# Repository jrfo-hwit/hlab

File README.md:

# H-Lab

**Laboratório educacional de sistemas embarcados HwIT**

Esta plataforma educacional de sistemas embarcados teve como base de sua placa principal (main_hw) o [BitDogLab](https://github.com/Fruett/BitDogLab) , um projeto totalmente aberto, que permite que os seus usuários copiem, fabriquem, montem e melhorem como bem entenderem.

Este repositório contem todas as informações das evoluções executadas pela HwIT no [BitDogLab](https://github.com/Fruett/BitDogLab) (versões 5.3, 6.0, 6.2, 6.3 - versão do programa [Embarcatech](https://embarcatech.softex.br/) e 6.4 - ultima evolução executada pela HwIT), a próxima versão em desenvolvimento será placa HLab 1.0.

## Placa principal

Além da placa principal [main_hw](./hardware/main_hw/bitdoglab_v6_4_main.pdf), existe a placa do painel frontal de conexão [front_panel_hw](./hardware/front_panel_hw/bitdoglab_v6_4_painel.pdf) compondo a solução [BitDogLab](https://github.com/Fruett/BitDogLab).

## Placas periféricas

Esse repositório apresenta os periféricos desenvolvidos para segunda fase do programa [Embarcatech](https://embarcatech.softex.br/), Os periféricos são compostos pelos seguintes componentes:

* Kit Básico de Periféricos (12 itens)
  * Periferico adaptador de sensores/atuadores
      * [Sensor i2c] Acelerômetro
      * [Sensor i2c] Oxímetro e batimentos cardiácos
      * [Sensor i2c] Medição de distância a Laser
      * [Sensor i2c] Temperatura e pressão
      * [Sensor i2c] Luminosidade
      * [Sensor i2c] Umidade e temperatura
      * [Sensor i2c] Cor RGB
      * [Atuador PWM] Servo Motor
  * Periférico HDMI
  * Periférico de extensão de conexões para sensores (i2c)
  * Periférico teclado matricial (GPIO)
  * Periférico de armazenamento de dados SDCARD (SPI)

* Kit Avançado de Periféricos (19 itens) = Kit Básico (12) + itens abaixo (7)
  * Periférico de extensão de conexões (SPI)
  * Periferico conversor analógico digital ADC / digital analógico DAC / GPIO com oito portas (SPI)
  * Periférico câmera de 2M Pixels (interface paralela)
  * Periférico display LCD 320x240 pixels (SPI)
  * Periférico comunicação radio de longa distância LoRA (SPI)
  * Periférico GPS (UART)
  * Periférico Pi Pico debug probe (SWD)
* Gerenciador de bateria bq25622 (i2c, embarcado na placa principal)

:warning: Acesse esse [link](https://github.com/jrfo-hwit/hlab/tree/main/hardware/peripherals_hw) para obter maiores detalhes sobre cada um dos periféricos

A Placa HLab 1.0 vai integrar a placa principal com o painel frontal, e será evoluida para atender não só as demandas de sistemas embarcados, mas também as demandas de inteligência artifical de borda (EDGE AI) e aprendizado de máquina (Machine Learning), toltamente integradas com os periféricos já desenvolvidos para plataforma atual.

## Micropython

:warning: Esse repositório contém firmwares do interpretador micropython compilado para RP2040 (Pi Pico e Pi Pico W) contida na placa principal, [acesse aqui os últimos releases](https://github.com/jrfo-hwit/hlab/tree/main/firmware/micropython/releases). Esse firmware contém além do micropython todas as bibliotecas necessárias para interagir com a placa principal e seus respectivos periféricos.

**A maneira mais fácil de começar se você é iniciante com a plataforma, é por meio da leitura do nosso [guia do iniciante](./firmware/micropython/README.md).**

## C/C++

Para usuários avançados que desejam utilizar todo o poder do processador RP2040 pode fazer o mesmo por meio da liguagem C++. Se vocês sabe o que está fazendo e gostaria de construir seu próprio projeto de firmware, você deve utilizar o SDK [Pi Pico](https://github.com/raspberrypi/pico-sdk) e pode utilizar nosso [projeto exemplo](https://github.com/jrfo-hwit/hlab/tree/main/firmware/c_cpp/boilerplate), ou se basear em nossos [exemplos de uso da placa principal e/ou periféricos](https://github.com/jrfo-hwit/hlab/tree/main/firmware/c_cpp/examples).

# Licença

Todas as versões BitDogLab estão sob a licença CERN Open Hardware Licence Version 2 - Strongly Reciprocal .
Para mais detalhes veja o arquivo `LICENSE`.

Os demais hardwares periféricos e a futura placa H-Lab estão sob a licença MIT . Para mais detalhes veja o arquivo `LICENSE`.

# Estrutura do Repositório

Segue abaixo a estrutura de arquivos desse repositório. 

O repositório se divide em firmware (código que controla o processador principal da BitDogLab/HLab) contendo tanto código micropython (usuários básicos) quanto c/c++ (usuários avançados), seguido do hardware eletrônico que contém as informações de todas as placas (principal, painel frontal e periféricos), seguido software contendo informações e código para plataforma low code, mecânica contendo peças e partes mecânicas de suporte ao hardware, e fechando com a pasta educacional contendo informações e material para treinamento de professores, instruturoes e alunos.

```bash
├───education "Arquivos e documentação para treinamentos e aprendizado"
│   ├───teacher "Materiais de treinamento para professores"
│   ├───instructor "Materiais de treinamento para instrutores"
│   └───student "Aulas para estudantes"
├───firmware "Nesta pasta ficam os arquivos do firmware, seja micropython ou c/c++"
│   └───micropython "Interpretador (arquivos fonte e uf2 para carregarmos na Pi Pico) e todos exemplos"
│       ├───micropython "Código fonte e compilado do interpretador micropython"
│       ├───pimoroni-pico "Código fonte pimoroni-pico, contendo bilbiotecas e micropython"
│       ├───releases "firmware compilado micropython"
│       └───examples "Arquivos de exemplo de firmware incluindo codigo fonte e documentação"
│   └───c_cpp "Aqui ficam os arquivos do SDK (submodule) e todos os exemplos"
│       ├───pico_sdk "Link simbolico para SDK"
│       └───examples "Arquivos de exemplo de firmware incluindo codigo fonte e documentação"
├───hardware "Aqui ficam todos os arquivos de hardware para placa principal, painel frontal e perifericos"
│   └───main_hw "Esquemático, Layout and Gerber da placa principal, arquivos de projeto"
│       ├───pcb "Arquivos de fabricação do PCB"
│       ├───3D "Arquivos 3D dos componentes da placa"
│       └───electronics "Datasheets e documentação de projeto"
│   ├───front_panel_hw "Esquemático, Layout and Gerber do painel frontal (quando existente), arquivos de projeto"
│       ├───pcb "Arquivos de fabricação do PCB"
│       ├───3D "Arquivos 3D dos componentes da placa"
│       └───electronics "Datasheets e documentação de projeto"
│   └───peripherals_hw "Esquemático, Layout and Gerber dos periféricos, arquivos de projeto"
│       ├───pcb "Arquivos de fabricação do PCB"
│       ├───3D "Arquivos 3D dos componentes da placa"
│       └───electronics "Datasheets e documentação de projeto"
├───mechanics "Modelos mecânicos para uso com placas da plataforma"
│   ├───main_mech "Partes mecanicas para uso com a placa principal"
│   └───peripherals_mech "Partes mecanicas para uso com os periféricos"
└───software "Softwares de auxilio ao uso da plataforma"
│   └───low_code "Ferramenta de programação em blocos (low code), codigo fonte, biblioteca e documentos"
```

# [Hardware Innovation Technologies](http://www.hwit.com.br/)

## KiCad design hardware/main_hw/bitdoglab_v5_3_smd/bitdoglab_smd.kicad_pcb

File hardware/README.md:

# HLab Hardware

Essa pasta apresenta detalhes sobre todos os relativos a plataforma HLAB e trabalhos anteriores no suporte da bitdoglab.

Basicamente com relação ao bitdoglab, suportamos a evolução da placa a partir da versão 5.3 até a versão 6.3 (embarcatech) e 6.4. Os arquivos esquemáticos da placa principal se encontram na pasta main_hw, nos seguintes links:

* bitdoglab 5.3 [esquemático](./main_hw/bitdoglab_v5_3_smd.pdf) e [código fonte (Kicad)](./main_hw/bitdoglab_v5_3_smd/)
* bitdoglab 6.0 [esquemático](./main_hw/bitdoglab_v6_0_smd.pdf)
* bitdoglab 6.2 [esquemático](./main_hw/bitdoglab_v6_2_smd.pdf)
* bitdoglab 6.3 - versão embarcatech [esquemático](./main_hw/bitdoglab_v6_3_smd-embarcatech.pdf)
* bitdoglab 6.4 [esquemático](./main_hw/bitdoglab_v6_4_main.pdf)

Os arquivos esquemáticos da placa do painel frontal se encontra na pasta front_panel_hw e no seguinte [link](./front_panel_hw/bitdoglab_v6_4_painel.pdf).

Os periféricos são compostos pelos seguintes componentes e seus respectivos links para os esquemáticos:

* Kit Básico de Periféricos (12 itens)
  * [Esquemático](./peripherals_hw/Adaptadora_R1.1.pdf) Periferico adaptador de sensores/atuadores
      * [Sensor i2c] Acelerômetro
      * [Sensor i2c] Oxímetro e batimentos cardiácos
      * [Sensor i2c] Medição de distância a Laser
      * [Sensor i2c] Temperatura e pressão
      * [Sensor i2c] Luminosidade
      * [Sensor i2c] Umidade e temperatura
      * [Sensor i2c] Cor RGB
      * [Atuador PWM] Servo Motor
  * [Esquemático](./peripherals_hw/bitdoglab-dvi-hdmi_v1r1.pdf) Periférico HDMI-DVI
  * [Esquemático](./peripherals_hw/I2C_Extender_R1.1.pdf) Periférico de extensão de conexões para sensores (i2c)
  * [Esquemático](./peripherals_hw/PRJ_Teclado.pdf) Periférico teclado matricial (GPIO)
  * [Esquemático](./peripherals_hw/LS_R1.1.pdf) Periférico de armazenamento de dados SDCARD (SPI)
* Kit Avançado de Periféricos (19 itens) = Kit Básico (12) + itens abaixo (7)
  * [Esquemático](./peripherals_hw/ADC_DAC_R1.1.pdf) Periferico conversor analógico digital ADC / digital analógico DAC / GPIO com oito portas (SPI)
  * [Esquemático](./peripherals_hw/CAMERA.pdf) Periférico câmera de 2M Pixels (interface paralela)
  * [Esquemático](./peripherals_hw/LCD_Rev1.2.pdf) Periférico display LCD 320x240 pixels (SPI)
  * [Esquemático](./peripherals_hw/LS_R1.1.pdf) Periférico comunicação radio de longa distância LoRA (SPI)
  * [Esquemático](./peripherals_hw/Adaptadora_R1.1.pdf) Periférico GPS (UART)
  * [Esquemático](./peripherals_hw/DEBUGGER_R1.1.pdf) Periférico Pi Pico debug probe (SWD)
  * [Esquemático](./peripherals_hw/IDC_Extender_R1.1.pdf) Periférico de extensão de conexões (SPI)
* Gerenciador de bateria bq25622 (i2c, embarcado na placa principal)

# [Hardware Innovation Technologies](http://www.hwit.com.br/)

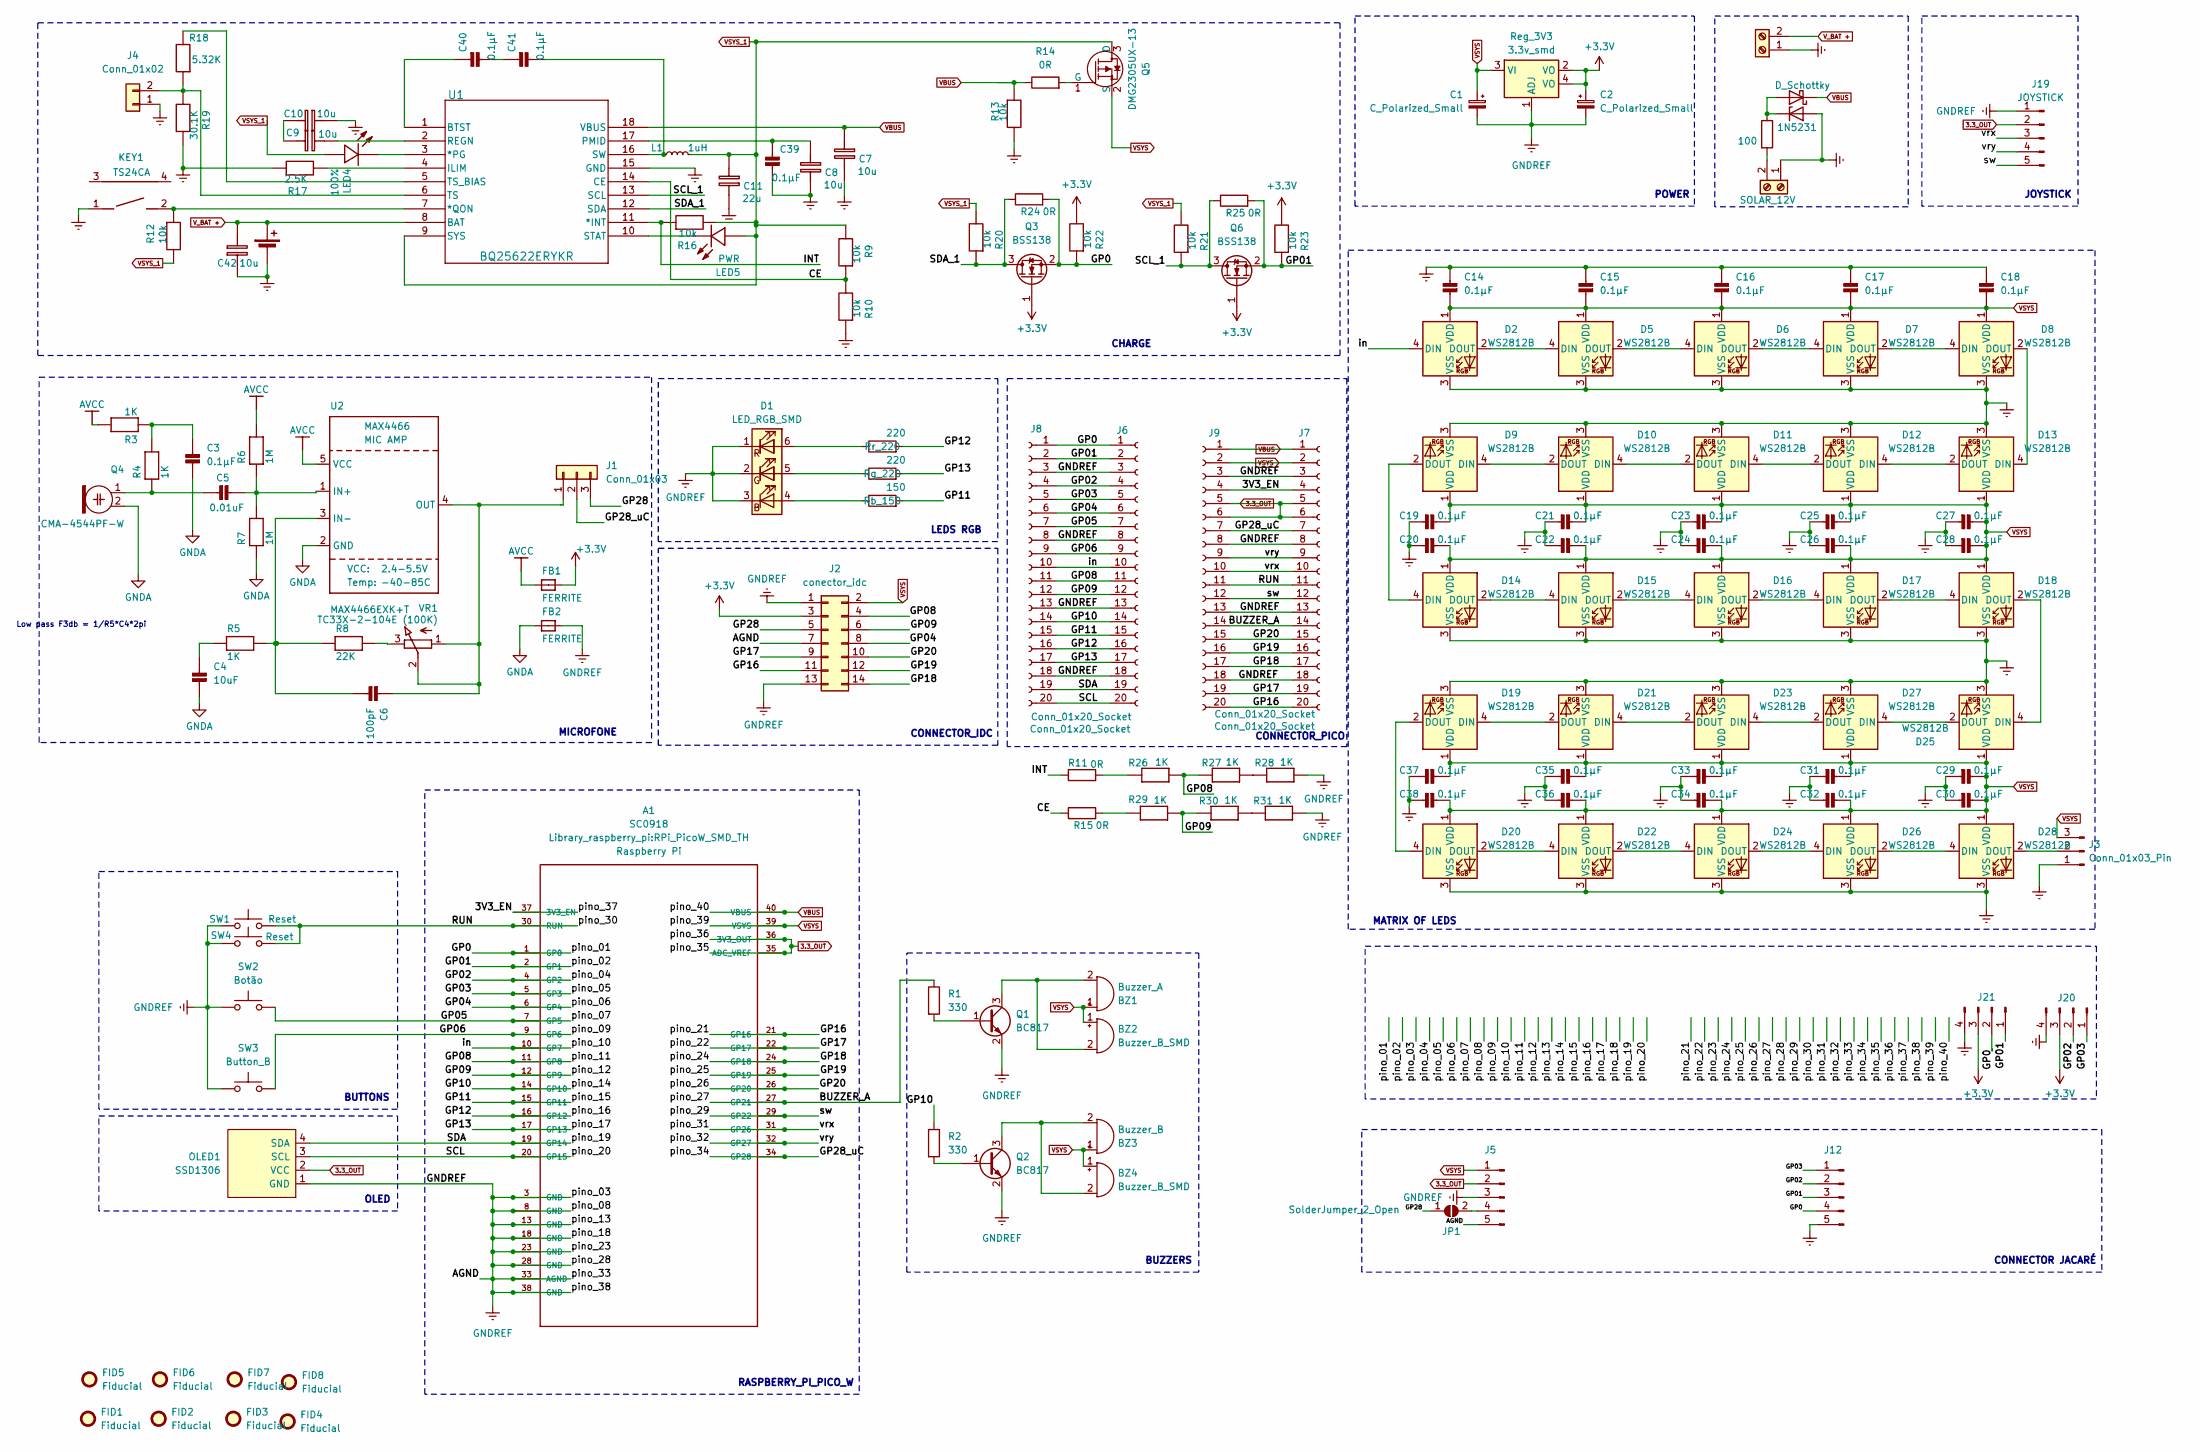
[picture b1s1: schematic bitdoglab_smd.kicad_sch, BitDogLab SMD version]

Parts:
A1: SC0918; RPi_PicoW_SMD_TH; PARTREV 1.6
BT1: Battery_Cell; BatteryHolder_MPD_BH-18650-PC2
BZ1: Buzzer_A; Buzzer_12x9.5RM7.6
BZ2, BZ4: Buzzer_B_SMD; MagneticBuzzer_CUI_CMT-8504-100-SMT
BZ3: Buzzer_B; Buzzer_12x9.5RM7.6
C1, C2: C_Polarized_Small; CP_Elec_5x5.9
C3, C14, C15, C16, C17, C18, C19, C20, C21, C22, C23, C24, C25, C26, C27, C28, C29, C30, C31, C32, C33, C34, C35, C36, C37, C38, C39, C40, C41: 0.1µF; C_0402_1005Metric
C4: 10uF; C_0805_2012Metric
C5: 0.01uF; C_0402_1005Metric
C6: 100pF; C_0402_1005Metric
C7, C8, C9, C10, C42: 10u; R_0805_2012Metric; MANUFACTURER PART CL21A106KAYNNNE
C11: 22u; R_0805_2012Metric; MANUFACTURER PART CL21A226MAQNNNE
CARGA_SOLAR1: SOLAR_12V; JST_EH_B2B-EH-A_1x02_P2.50mm_Vertical
D1: LED_RGB_SMD; LED_RGB_5050-6
D2, D5, D6, D7, D8, D9, D10, D11, D12, D13, D14, D15, D16, D17, D18, D19, D20, D21, D22, D23, D24, D25, D26, D27, D28: WS2812B; LED_WS2812B_PLCC4_5.0x5.0mm_P3.2mm
D3: 1N5231; D_T-1_P5.08mm_Horizontal
D4: D_Schottky; D_SOD-123
FB1, FB2: FERRITE; L_0603_1608Metric
FID1, FID2, FID3, FID4, FID5, FID6, FID7, FID8: Fiducial; Fiducial_1mm_Mask2mm
J1: Conn_01x03; PinHeader_1x03_P2.54mm_Vertical
J2: conector_idc; PinHeader_2x07_P2.54mm_Vertical
J3: Conn_01x03_Pin; PinHeader_1x03_P2.54mm_Vertical
J4: Conn_01x02; PinHeader_1x02_P2.54mm_Vertical
J5, J12: Conn_01x05_Pin; PinHeader_1x05_P2.54mm_Vertical
J6, J7, J8, J9: Conn_01x20_Socket; PinSocket_1x20_P2.54mm_Vertical_SMD_Pin1Right
J19: JOYSTICK; ky-023
J20, J21: Conn_01x04_Pin; JST_EH_B4B-EH-A_1x04_P2.50mm_Vertical
JP1: SolderJumper_2_Open; SolderJumper-2_P1.3mm_Open_TrianglePad1.0x1.5mm
KEY1: TS24CA; SW_SPST_CK_KMS2xxGP; MANUFACTURER PART TS24CA
L1: 1uH; L_Bourns_SRP7028A_7.3x6.6mm
LED4: 100%; LED_0805_2012Metric; MANUFACTURER PART 0805G (Green)
LED5: PWR; LED_0805_2012Metric; MANUFACTURER PART ORH-B35A
OLED1: SSD1306; 128x64OLED
Q1, Q2: BC817; SOT-23
Q3, Q6: BSS138; SOT-23
Q4: CMA-4544PF-W; Buzzer_12x9.5RM7.6
Q5: DMG2305UX-13; SOT-23-3; MPN DMG2305UX-13; Digi-Key_PN DMG2305UX-13DICT-ND
R1, R2: 330; R_0603_1608Metric
R3, R4, R5, R26, R27, R28, R29, R30, R31: 1K; R_0603_1608Metric
R6, R7: 1M; R_0603_1608Metric
R8: 22K; R_0603_1608Metric
R9, R10, R12, R13, R16, R20, R21, R22, R23: 10k; R_0603_1608Metric; MANUFACTURER PART 0805W8F1002T5E
R11, R14, R15, R24, R25: 0R; R_0603_1608Metric
R17: 2.5K; R_0603_1608Metric; MANUFACTURER PART RNCF0805DTE2K50
R18: 5.32K; R_0603_1608Metric
R19: 30.1K; R_0603_1608Metric; MANUFACTURER PART RNCF0805DTE2K50
R_1W1: 100; R_0603_1608Metric
Rb_150: 150; R_0603_1608Metric
Reg_3V3: 3.3v_smd; SOT-223
Rg_220: 220; R_0603_1608Metric
Rr_220: 220; R_0603_1608Metric
SW1: Reset; SW_PUSH_6mm
SW2: Botão; SW_PUSH_6mm_b
SW3: Button_B; SW_PUSH_6mm_b
SW4: Reset; SW_Push_1P1T_NO_6x6mm_H9.5mm
U1: BQ25622ERYKR; WQFN-HR18_RYK_TEX
U2: MAX4466EXK+T; SOT-353_SC-70-5
VR1: TC33X-2-104E (100K); Potentiometer_Bourns_TC33X_Vertical
V_BAT1: V_BAT; JST_EH_B2B-EH-A_1x02_P2.50mm_Vertical

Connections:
3.3_OUT: A1.35 (ADC_VREF), A1.36 (3V3_OUT), J5.2, J7.5, J7.6, J9.5, J9.6, J19.2, OLED1.2 (VCC)
+3.3V: C2.1, FB1.2, J2.3, J20.3, J21.3, Q3.1 (G), Q6.1 (G), R22.2, R23.2, Reg_3V3.2 (VO), Reg_3V3.4 (VO)
/3V3_EN: A1.37 (3V3_EN), J7.4, J9.4
/BUZZER_A: A1.27 (GP21), J7.14, J9.14, R1.1
/CE: R9.1, R10.2, R15.1, U1.14 (CE)
/GP0: A1.1 (GP0), J6.1, J8.1, J12.4, J21.2, Q3.2 (S), R22.1, R24.2
/GP01: A1.2 (GP1), J6.2, J8.2, J12.3, J21.1, Q6.2 (S), R23.1, R25.2
/GP02: A1.4 (GP2), J6.4, J8.4, J12.2, J20.2
/GP03: A1.5 (GP3), J6.5, J8.5, J12.1, J20.1
/GP04: A1.6 (GP4), J2.8, J6.6, J8.6
/GP05: A1.7 (GP5), J6.7, J8.7, SW2.1
/GP06: A1.9 (GP6), J6.9, J8.9, SW3.1
/GP08: A1.11 (GP8), J2.4, J6.11, J8.11, R26.1, R27.2
/GP09: A1.12 (GP9), J2.6, J6.12, J8.12, R29.1, R30.2
/GP10: A1.14 (GP10), J6.14, J8.14, R2.1
/GP11: A1.15 (GP11), J6.15, J8.15, Rb_150.2
/GP12: A1.16 (GP12), J6.16, J8.16, Rr_220.2
/GP13: A1.17 (GP13), J6.17, J8.17, Rg_220.2
/GP16: A1.21 (GP16), J2.11, J7.20, J9.20
/GP17: A1.22 (GP17), J2.9, J7.19, J9.19
/GP18: A1.24 (GP18), J2.14, J7.17, J9.17
/GP19: A1.25 (GP19), J2.12, J7.16, J9.16
/GP20: A1.26 (GP20), J2.10, J7.15, J9.15
/GP28: J1.3, J2.5, JP1.1 (A)
/GP28_uC: A1.34 (GP28), J1.2, J7.7, J9.7
/INT: R11.1, R16.1, U1.11 (*INT)
/RUN: A1.30 (RUN), J7.11, J9.11, SW1.1, SW4.1
/SCL: A1.20 (GP15), J6.20, J8.20, OLED1.3 (SCL)
/SCL_1: Q6.3 (D), R21.1, R25.1, U1.13 (SCL)
/SDA: A1.19 (GP14), J6.19, J8.19, OLED1.4 (SDA)
/SDA_1: Q3.3 (D), R20.1, R24.1, U1.12 (SDA)
/in: A1.10 (GP7), D2.4 (DIN), J6.10, J8.10
/pino_29: A1.29 (GP22), J7.12, J9.12, J19.5
/pino_31: A1.31 (GP26), J7.10, J9.10, J19.3
/pino_32: A1.32 (GP27), J7.9, J9.9, J19.4
AVCC: FB1.1, R3.2, R6.2, U2.5 (VCC)
GNDA: C3.2, C4.2, FB2.1, Q4.2 (+), R7.1, U2.2 (GND)
GNDREF: A1.3 (GND), A1.8 (GND), A1.13 (GND), A1.18 (GND), A1.23 (GND), A1.28 (GND), A1.33 (AGND), A1.38 (GND), BT1.2 (-), C1.2, C2.2, C7.2, C8.2, C10.2, C11.2, C14.1, C15.1, C16.1, C17.1, C18.1, C19.1, C20.1, C21.1, C22.1, C23.1, C24.1, C25.1, C26.1, C27.1, C28.1, C29.1, C30.1, C31.1, C32.1, C33.1, C34.1, C35.1, C36.1, C37.1, C38.1, C39.2, C42.1, CARGA_SOLAR1.1, D1.1 (RK), D1.2 (GK), D1.3 (BK), D2.3 (VSS), D3.2 (A), D5.3 (VSS), D6.3 (VSS), D7.3 (VSS), D8.3 (VSS), D9.3 (VSS), D10.3 (VSS), D11.3 (VSS), D12.3 (VSS), D13.3 (VSS), D14.3 (VSS), D15.3 (VSS), D16.3 (VSS), D17.3 (VSS), D18.3 (VSS), D19.3 (VSS), D20.3 (VSS), D21.3 (VSS), D22.3 (VSS), D23.3 (VSS), D24.3 (VSS), D25.3 (VSS), D26.3 (VSS), D27.3 (VSS), D28.3 (VSS), FB2.2, J2.1, J2.7, J2.13, J3.1, J4.1, J5.3, J5.5, J6.3, J6.8, J6.13, J6.18, J7.3, J7.8, J7.13, J7.18, J8.3, J8.8, J8.13, J8.18, J9.3, J9.8, J9.13, J9.18, J12.5, J19.1, J20.4, J21.4, KEY1.1, OLED1.1 (GND), Q1.2 (E), Q2.2 (E), R10.1, R13.2, R17.1, R19.1, R28.1, R31.1, Reg_3V3.1 (ADJ), SW1.2, SW2.2, SW3.2, SW4.2, U1.15 (GND), V_BAT1.1
unnamed: BZ1.2 (+), BZ2.2 (+), Q1.3 (C)
unnamed: BZ3.2 (+), BZ4.2 (+), Q2.3 (C)
unnamed: C3.1, R3.1, R4.2
unnamed: C4.1, R5.1
unnamed: C5.1, Q4.1 (-), R4.1
unnamed: C5.2, R6.1, R7.2, U2.1 (IN+)
unnamed: C6.1, J1.1, U2.4 (OUT), VR1.1 (A), VR1.2 (S)
unnamed: C6.2, R5.2, R8.1, U2.3 (IN-)
unnamed: C9.1, C10.1
unnamed: C8.1, C39.1, U1.17 (PMID)
unnamed: C40.1, U1.1 (BTST)
unnamed: C40.2, C41.1
unnamed: C41.2, L1.1, U1.16 (SW)
unnamed: CARGA_SOLAR1.2, R_1W1.2
unnamed: D1.4 (BA), Rb_150.1
unnamed: D1.5 (GA), Rg_220.1
unnamed: D1.6 (RA), Rr_220.1
unnamed: D2.2 (DOUT), D5.4 (DIN)
unnamed: D3.1 (K), D4.2 (A), R_1W1.1
unnamed: D5.2 (DOUT), D6.4 (DIN)
unnamed: D6.2 (DOUT), D7.4 (DIN)
unnamed: D7.2 (DOUT), D8.4 (DIN)
unnamed: D10.4 (DIN), D11.2 (DOUT)
unnamed: D9.4 (DIN), D10.2 (DOUT)
unnamed: D11.4 (DIN), D12.2 (DOUT)
unnamed: D12.4 (DIN), D13.2 (DOUT)
unnamed: D8.2 (DOUT), D13.4 (DIN)
unnamed: D9.2 (DOUT), D14.4 (DIN)
unnamed: D14.2 (DOUT), D15.4 (DIN)
unnamed: D15.2 (DOUT), D16.4 (DIN)
unnamed: D16.2 (DOUT), D17.4 (DIN)
unnamed: D17.2 (DOUT), D18.4 (DIN)
unnamed: D18.2 (DOUT), D25.4 (DIN)
unnamed: D19.4 (DIN), D21.2 (DOUT)
unnamed: D19.2 (DOUT), D20.4 (DIN)
unnamed: D20.2 (DOUT), D22.4 (DIN)
unnamed: D21.4 (DIN), D23.2 (DOUT)
unnamed: D22.2 (DOUT), D24.4 (DIN)
unnamed: D23.4 (DIN), D27.2 (DOUT)
unnamed: D24.2 (DOUT), D26.4 (DIN)
unnamed: D25.2 (DOUT), D27.4 (DIN)
unnamed: D26.2 (DOUT), D28.4 (DIN)
unnamed: D28.2 (DOUT), J3.2
unnamed: J4.2, R18.1, R19.2, U1.6 (TS)
unnamed: J5.4, JP1.2 (B)
unnamed: LED4.2 (K), U1.3 (*PG)
unnamed: LED5.2 (K), U1.10 (STAT)
unnamed: Q1.1 (B), R1.2
unnamed: Q2.1 (B), R2.2
unnamed: Q5.1 (G), R14.2
unnamed: R11.2, R26.2
unnamed: R15.2, R29.2
unnamed: R27.1, R28.2
unnamed: R30.1, R31.2
unnamed: KEY1.2, R12.1, U1.7 (*QON)
unnamed: R17.2, U1.4 (ILIM)
unnamed: C9.2, U1.2 (REGN)
unnamed: R18.2, U1.5 (TS_BIAS)
unnamed: R8.2, VR1.3 (E)
VBUS: A1.40 (VBUS), C7.1, D4.1 (K), J7.1, J9.1, R13.1, R14.1, U1.18 (VBUS)
VSYS: A1.39 (VSYS), BZ1.1 (-), BZ2.1 (-), BZ3.1 (-), BZ4.1 (-), C1.1, C14.2, C15.2, C16.2, C17.2, C18.2, C19.2, C20.2, C21.2, C22.2, C23.2, C24.2, C25.2, C26.2, C27.2, C28.2, C29.2, C30.2, C31.2, C32.2, C33.2, C34.2, C35.2, C36.2, C37.2, C38.2, D2.1 (VDD), D5.1 (VDD), D6.1 (VDD), D7.1 (VDD), D8.1 (VDD), D9.1 (VDD), D10.1 (VDD), D11.1 (VDD), D12.1 (VDD), D13.1 (VDD), D14.1 (VDD), D15.1 (VDD), D16.1 (VDD), D17.1 (VDD), D18.1 (VDD), D19.1 (VDD), D20.1 (VDD), D21.1 (VDD), D22.1 (VDD), D23.1 (VDD), D24.1 (VDD), D25.1 (VDD), D26.1 (VDD), D27.1 (VDD), D28.1 (VDD), J2.2, J3.3, J5.1, J7.2, J9.2, Q5.2 (S), Reg_3V3.3 (VI)
VSYS_1: C11.1, L1.2, LED4.1 (A), LED5.1 (A), Q5.3 (D), R9.2, R12.2, R16.2, R20.2, R21.2, U1.9 (SYS)
V_BAT +: BT1.1 (+), C42.2, U1.8 (BAT), V_BAT1.2

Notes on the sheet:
POWER
OLED
BUZZERS
LEDS RGB
BUTTONS
CONNECTOR_IDC
CONNECTOR JACARÉ
Low pass F3db = 1/R5*C4*2pi
CONNECTOR_PICO
CHARGE
MICROFONE
MATRIX OF LEDS
RASPBERRY_PI_PICO_W
JOYSTICK

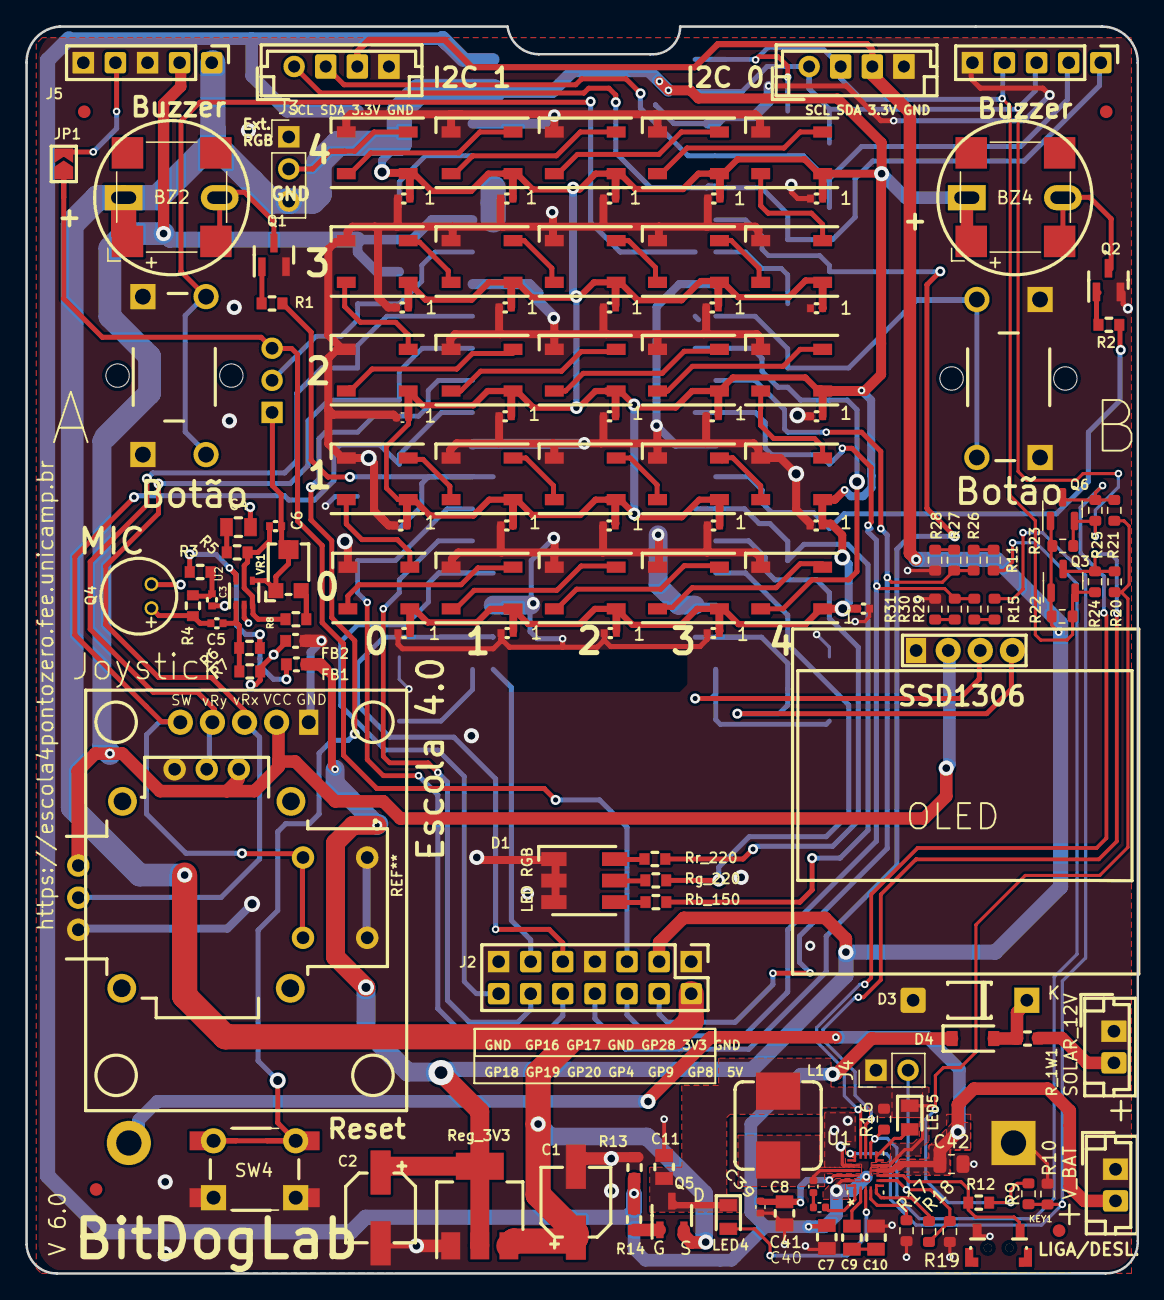
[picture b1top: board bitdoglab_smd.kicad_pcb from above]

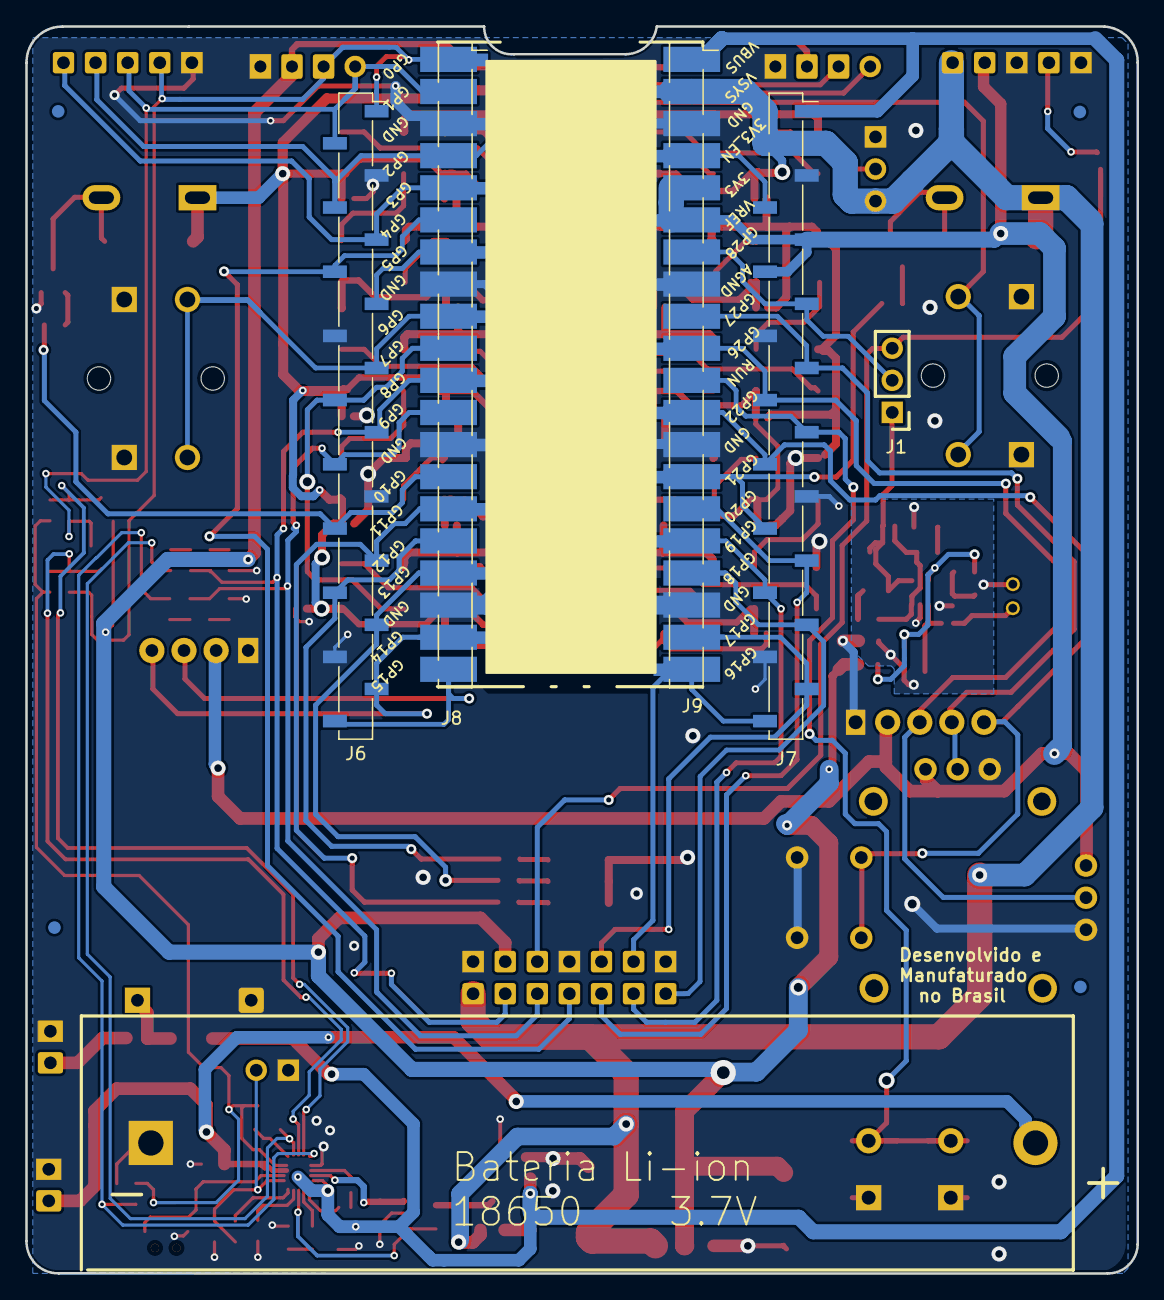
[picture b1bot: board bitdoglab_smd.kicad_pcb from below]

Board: 2 copper layers, 87.9 x 98.7 mm, 154 parts (11 on the bottom side), 101 nets.

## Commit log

2025-04-14 HLAB main docs and repository structure.
2025-04-14 adding gitignore file
2025-04-20 Updated README.md, updated file structure, included submodules pico-sdk, pimoroni-pico and micropython.
2025-04-23 compiled firmware releases for micropython (with picographics only, lacking other peripherals), adjustments on main README.md, partial filling of peripherals hardware README.md and images at hardware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
2025-04-25 Detalhes do readme.md com documentação dos hardwares periféricos (até o teclado), pasta docs com datasheets.
2025-04-28 Primeira versão completa da documentação de hardware dos periféricos
2025-05-06 Documentação exemplos periféricos micropython e iniciando com micropython
2025-05-06 Ajustes no README principal e o mesmo do peripherals_hw
2025-05-06 ajuste de tamanho de imagens no readme iniciando com micropython
2025-05-06 Atualização de documentação de firmware e hardware, adição de esquemáticos de versões anteriores da bitdoglab evoluídas pela HwIT e adição do projeto da bitdoglab versão 5.3
2025-05-06 esquemático bitdoglab 6.3 smd
2025-05-06 problema com esquematico bitdoglab 6.3 embarcatech
2025-05-08 micropython compilation cmakes and image sizing reduction
2025-05-12 Atualização de projeto bitdoglab 5.3 e esquemáticos bitdoglab 5.3 e bitdoglab 6.2
2025-05-21 VsCode Examples C/C++ HDMI peripheral
2025-06-03 Debugprobe project and firmware.
2025-08-07 Adjust of resolution at HDMI examples to 640x480 for means of compatibility test with any display (lowest know resolution that every display support).
2025-08-07 LVGL 9.4 LCD C example code considering ST7789 LCD from peripheral and Raspberry pi pico W (bitdoglab 6.4) with LVGL. ST7789 driver implemented in PIO, GUI was generated by EEZ Studio software.
2025-08-07 Release uf2 for lcd pio st7789 + lvgl demo with image and slider
2025-08-07 EEZ Studio project for landscape UI screen for LCD pio LVGL image slider demo
2025-08-08 Documentation for 2_LCD_pio_LVGL_img_slider_button demo
2025-08-10 Example for AHT10 temperature & humidity sensor through I2C1 printing over UART0 @ 115200 8n1
2025-08-10 Example for BMP280 pressure and temperature sensor communicating over i2c and sending information through UART0 115200 8n1
2025-08-10 Demo of VL53L0X dToF laser distance measurement sensor on i2c1 and data print on uart0.
2025-08-11 Demo of MPU-6050 from Raspberry pi examples separating the mpu6050.c and .h files to better organization.
2025-08-11 Demo of BH1750 luminosity sensor at i2c1 sending information through UART0 @ 115200 8n1
2025-08-11 Demo of MAX3010x heartbeat and SPO2 sensor through i2c1 with data being reported at uart0 115200 8n1.
2025-08-20 removing local copy of lvgl pi pico
2025-08-20 add lvgl for pi pico as submodule
2025-08-20 C_CPP example 9: LVGL updating data of temperature and humidity sensors live on LCD screen
2025-08-21 removed old-ui, added eez lvgl gui project
2025-08-25 Updated project with second screen with temperature and humidity chart with 1 day measurement history.
2025-08-26 Added README.md for c/c++ example 9 : AHT10 + ST7789 LCD + LVGL Temperature, Humidity & Dew Point Monitor
2025-08-27 Refreshed image on c/c++ example 9: st7789 pio lcd LVGL humidity and temperature.
2025-10-11 made in c_cpp example 9: inserted demo mode define (every 7 seconds change screens), corrected chart initialization with default values (changed position of initialization and calculation on the code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
2025-10-13 LCD ST7789 320x480 pixels project (it is very similar to st7789 with difference of reduce to single buffer on lv_port_display_init at main.c to use less memory, and the lcd init configurations on st7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
2025-10-13 LCD ST7796 320x480 pixels project (it is very similar to st7789 with difference of reduce to single buffer on lv_port_display_init at main.c to use less memory, and the lcd init configurations on st7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
2025-11-23 Add comprehensive README.md for ST7796 LCD LVGL project
    - Created detailed documentation for example 10 (ST7796 480x320 display)
    - Documented key differences from ST7789 version (example 9)
    - Included hardware requirements and pin connections
    - Added software configuration and build instructions
    - Documented memory optimization strategy (single buffer)
    - Included ST7796-specific initialization settings

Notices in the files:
README.md:
License: CERN-OHL-S v2.0
